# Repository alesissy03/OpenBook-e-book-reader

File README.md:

# OpenBook-e-book-reader

# Project Structure
```
OpenBook E-Reader
├── Hardware
│ ├── E-Reader.sch
│ └── E-Reader.brd
├── Manufacturing
│ ├── gerbers.zip
│ ├── bom.csv
│ └── pap.csv
├── Mechanical
│ ├── E-Reader.zip # STEP model archive
│ ├── E-Reader.f3z
│ └── OpenBook Enclosure.f3d # Enclosure model
├── Images
│ ├── 3d.png
│ ├── Schematic.png
│ ├── Board.png
│ └── Board_in_box.png
├── LICENSE # Apache 2.0
└── README.md
```

# Bill of Materials

## Component List

| Name                          | Description                                                                                           | Value        | Quantity | Link to buy| Datasheet |
|-------------------------------|----------------------------------------------------------------------------|--------------|----------|------|------------------|
| 744043680                     | IND_4828-WE-TPC_WRE                                              | 68uH         | 1        | https://mou.sr/42yVhMe     | https://www.we-online.com/components/products/datasheet/744043680.pdf |
| 112A-TAAR-RO3_ATTEND          | Micro SD Card Socket, Push-Push Type, Top Mount, SMT, H = 1.83mm | 10u          | 1        | https://www.attend.com.tw/en/product.php?act=view&id=253# | https://www.attend.com.tw/data/download/file/112A-TAAR-R03_Spec.pdf |
| BD5229G-TR                    | Voltage Detector with Adjustable Delay Time (CMOS)               |              | 1        | https://mou.sr/421TSO9     | https://fscdn.rohm.com/en/products/databook/datasheet/ic/power/voltage_detector/bd52xxg-e.pdf |
| BUTTON_CUSYOMV1               | Momentary Switch (Pushbutton) – SPST – SMD, 4.6 x 2.8mm          |              | 3        | https://mou.sr/41Yc6zX     | https://4donline.ihs.com/images/VipMasterIC/IC/PANA/PANA-S-A0000771493/PANA-S-A0000771493-1.pdf? hkey=CECEF36DEECDED6468708AAF2E19C0C6 |
| CPH3225A                      | Capacitor 0.011F 3.3V 1210 Flat                                  |              | 1        | https://mou.sr/42aoXOc     | https://ro.mouser.com/datasheet/2/360/Seiko_Instruments_MicroBattery_E_20230330_2024Jan_-3561061.pdf |
| DS3231SN#                     | Real Time Clock Serial 16-Pin SOIC W T/R                         |              | 1        | https://mou.sr/4ll9PXb     | https://ro.mouser.com/datasheet/2/609/DS3231-3421123.pdf |
| EAGLE-LTSPICE_CC0402         | Capacitor                                                         | 100nF        | 8        | https://mou.sr/42aprE0     | https://www.mouser.com/catalog/specsheets/Kemet_2-4-2024_KEM_F3140_R41D_Y2_300%20(draft3)%20(3).pdf?_gl=1*1rt35nv*_gcl_au*OTQ1MTI5Nzc4LjE3NDM5NjUwNTA.*_ga*MTkwMDk4MTgwMy4xNzQzOTY1MDUx*_ga_15W4STQT4T*MTc0NDc3OTk1NS4zLjEuMTc0NDc4MTkwNi4xOS4wLjA. |
| EAGLE-LTSPICE_CC0402         | Capacitor                                                         | 4.7uF        | 5        | https://mou.sr/44lcHNw     | https://ro.mouser.com/datasheet/2/40/AutoMLCCKAM-3216307.pdf |
| EAGLE-LTSPICE_CC0402         | Capacitor                                                         | 10uF         | 1        | https://mou.sr/3G8LNhS     | https://ro.mouser.com/datasheet/2/40/cx5r_KGM-3223198.pdf |
| EAGLE-LTSPICE_CC0402         | Capacitor                                                         | 1uF/50V      | 9        | https://mou.sr/3YwHHGK     | https://ro.mouser.com/datasheet/2/447/upy_gphc_x5r_4v_to_50v-3461255.pdf |
| EAGLE-LTSPICE_CC0402         | Capacitor                                                         | 0.1uF/50V    | 1        | https://mou.sr/3RC3wkl     | https://product.tdk.com/system/files/dam/doc/product/capacitor/ceramic/mlcc/catalog/mlcc_commercial_midvoltage_en.pdf |
| EAGLE-LTSPICE_CC0402         | Capacitor                                                         | 1nF          | 1        | https://mou.sr/3YwHHGK     | https://ro.mouser.com/datasheet/2/447/upy_gphc_x5r_4v_to_50v-3461255.pdf |
| ESP32_WROVER_BME680_BME680   | Integrated Environmental Unit (BME680)                            |              | 1        | https://mou.sr/42kgEzJ     | https://ro.mouser.com/datasheet/2/783/BST_BME680_DS001-1509608.pdf |
| ESP32_WROVER_AVX---          | Schotty Barrier Rectifier Diode                                   |              | 1        |                            |
| ESP32_WROVER_RR0402          | Resistor                                                          | 10k          | 15       | https://mou.sr/4i5Vvim     | https://www.vishay.com/docs/53046/pfrr.pdf |
| ESP32_WROVER_RR0402          | Resistor                                                          | 2.2          | 1        | https://mou.sr/4i9Xsun     | https://www.vishay.com/docs/53046/pfrr.pdf |
| ESP32_WROVER_RR0402          | Resistor                                                          | 0.47         | 1        | https://mou.sr/4i9XAKn     | https://www.vishay.com/docs/53046/pfrr.pdf |
| ESP32_WROVER_RR0402          | Resistor                                                          | 200          | 1        | https://mou.sr/4i9XAKn     | https://www.vishay.com/docs/53046/pfrr.pdf |
| ESP32_WROVER_RR0402          | Resistor                                                          | 2k           | 1        | https://mou.sr/4jeq8Do     | https://www.vishay.com/docs/53046/pfrr.pdf |
| ESP32_WROVER_RR0402          | Resistor                                                          | 15           | 1        | https://mou.sr/4i5Vvim     | https://www.vishay.com/docs/53046/pfrr.pdf |
| ESP32_WROVER_RR0402          | Resistor                                                          | 5k1          | 2        | https://mou.sr/4jeq8Do     | https://www.vishay.com/docs/53046/pfrr.pdf |
| ESP32_WROVER_RR0402          | Resistor                                                          | 100k         | 1        | https://mou.sr/4jeq8Do     | https://www.vishay.com/docs/53046/pfrr.pdf |
| ESP32_WROVER_SPARKFUN-       | P-channel MOSFETs                                                 |              | 2        | https://mou.sr/42jyNxv     | https://ro.mouser.com/datasheet/2/268/MCP73831_Family_Data_Sheet_DS20001984H-3441711.pdf |
| ESP32_WROVER_SPARKFUN-IC-    | MCP73831T Li-Ion, Li-Pol Controller                               |              | 1        | https://mou.sr/42jyNxv     | https://ro.mouser.com/datasheet/2/268/MCP73831_Family_Data_Sheet_DS20001984H-3441711.pdf |
| ESP32C6_VARISTORCN1812       | Varistor                                                          |              | 1        | https://mou.sr/3RnbVYV     | https://www.tdk-electronics.tdk.com/inf/75/db/CTVS_14/Surge_protection_series.pdf |
| ESP32-C6-WROOM-1-N8          |                                                                   |              | 1        | https://mou.sr/42swLfH     | https://ro.mouser.com/datasheet/2/891/Espressif_ESP32_C6_WROOM_1__Datasheet_V0_1_PRELIMI-3239987.pdf |
| FH34SRJ-24S-0.5SH_99_        | 24-pos FFC/FPC Connector, Right Angle                             |              | 1        |  https://mou.sr/43Cr53R    | https://ro.mouser.com/datasheet/2/185/FH34SRJ_24S_0_5SH_99__CL0580_1255_6_99_2DDrawing_0-1615044.pdf |
| MAX17048G+T10                | Fuel Gauge                                                        |              | 1        | https://mou.sr/3FWR5wY     | https://ro.mouser.com/datasheet/2/609/MAX17048_MAX17049-3469099.pdf |
| MBR0530                       | Diode, Schottky, 0.5A, 30V, SOD-123                              |              | 2        | https://mou.sr/4jmza1b     | https://www.onsemi.com/download/data-sheet/pdf/mbr0530t1-d.pdf |
| PGB1010603MR                  | ESD Suppressor                                                   |              | 6        | https://mou.sr/3Yg9sDe     | https://www.littelfuse.com/assetdocs/pulseguard-esd-suppressors-pgb1-datasheet?assetguid=8a337998-d54d-466b-be4e-dc5bcd1f9321 |
| QWIIC_CONNECTORJS-1MM        | I²C Standard Qwiic Connector                                      |              | 1        | https://www.sparkfun.com/qwiic-jst-connector-smd-4-pin-horizontal.html | https://cdn.sparkfun.com/assets/parts/1/2/2/8/9/Qwiic_Connector_Datasheet.pdf |
| RCL_CPOL-EUCT3528            | Polarized Capacitor (Tantalum)                                    | 100uF TANT   | 1        | https://mou.sr/42webCl     | https://www.mouser.com/catalog/specsheets/Panasonic_08082018_Capacitor%20Radial%20Leaded%20Lytic%20(EEU-FS)%20020118.pdf?_gl=1*1qqq4o9*_gcl_au*OTQ1MTI5Nzc4LjE3NDM5NjUwNTA.*_ga*MTkwMDk4MTgwMy4xNzQzOTY1MDUx*_ga_15W4STQT4T*MTc0NDc3OTk1NS4zLjEuMTc0NDc4MjQ0MS4zOC4wLjA. |
| SAMACSYS_USB4110-GF-A        | USB 2.0 Type-C Connector, Right Angle SMT                         |              | 1        | https://www.digikey.ro/en/products/detail/gct/USB4110-GF-A/10384547     | https://gct.co/files/specs/usb4110-spec.pdf?v=6b2a6292-70a5-4bd5-a7e5-0f3fe03e015f |
| SI1308EDL-T1-GE3              | MOSFET N-Ch 30V 1.5A Vishay TrenchFET                            |              | 1        | https://mou.sr/4lj7JXH     | https://www.vishay.com/docs/63399/si1308edl.pdf |
| SJ                            | SMD Solder Jumper                                                |              | 1        | https://mou.sr/42luaTB     | https://ro.mouser.com/datasheet/2/972/cjs-1827353.pdf |
| USBLC6-2SC6Y                 | ESD Protection Diode Array, 6-Pin SOT-23                          |              | 1        | https://mou.sr/42lyiTK     | https://ro.mouser.com/datasheet/2/389/usblc6_2sc6y-1852505.pdf |
| W25Q512JVEIQ                 | Flash Memory                                                      |              | 1        | https://mou.sr/42vsB6J     | https://ro.mouser.com/datasheet/2/949/Winbond_W25Q512JV_Datasheet-3240039.pdf |
| XC6220A331MR-G               | LDO Voltage Regulator                                             |              | 1        | https://mou.sr/4ieKgVa     | https://ro.mouser.com/ProductDetail/Torex-Semiconductor/XC6220A331MR-G?qs=AsjdqWjXhJ8ZSWznL1J0gg%3D%3D |

# ESP32 C6

| Pin        | Name | Label|  Function             | Connection to  |
|------------|-------|----------|----------------------|----------------|
| 1 | GND | - | Ground | Ground |
| 2 | 3V3 | - | Power | 3.3V |
| 3 | EN | RESET |Reset | Pull-up to 3.3v |
| 4 | IO4 | SS_SD | SD card chip select | J4 |
| 5 | IO5 | EPD_DC | E-Paper Display Command | J4 |
| 6 | IO6 | SCK | SPI Clock | J3, J4 |
| 7 | IO7 | MOSI | Master Out Slave In | J3, J4 |
| 8 | IO0 | INT_RTC | RTC Interrupt | DS3231SN |
| 9 | IO1 | 32KHZ | 32 kHz output | DS3231SN |
| 10 | IO8 | - | Power | 3.3V |
| 11 | IO10 | EPD_CS | E-Paper Display Chip Select | J3 |
| 12 | IO11 | FLASH_CS | Exernal NOR Flash Chip Select | J4 |
| 13 | IO12 | USB_D- | USB D- | J2 via D2 |
| 14 | IO13 | USB_D+ | USB D+ | J2 via D2 |
| 15 | IO9 | IO/BOOT | BOOT button | BOOT button
| 16 | IO18 | RTC_RST | RTC Module Reset | DS3231SN |
| 17 | IO19 | I2C_PW | Power | BME688 Sensor |
| 18 | IO20 | EPD_3V3_C | E-Paper Display Power | 
| 19 | IO21 | SDA | Battery Level
| 20 | IO22 | SCL | Battery Level
| 21 | IO23 | EPD_RST | E-Paper Display Reset | J4
| 22 | NC | - | - | -
| 23 | IO15 | IO/CHANGE | Change button | Change Button
| 24 | RXD0/GPIO17 | RX | UART EX
| 25 | TXD0/GPIO16 | TX | UART TX
| 26 | IO3 | EPD_BUSY | E-Paper Display Busy signal | J4
| 27 | IO2 | MISO | Master In Slave Out | J3, J4   

# Errors and warnings
During the design process in Autodesk Fusion, several warnings were flagged in both the schematic and PCB layouts. Below is a summary of the warnings I reviewed and explicitly approved based on the context of this project:

## Schematic (only warnings, no errors)
### "POWER pin X connected to Y" Warnings
- VBAT is supplied via a battery circuit
- 3V3 is regulated by a dedicated LDO
- I2C_PW and other power rails are driven by appropriate sources
- All GND connections are correctly tied to a common ground plane
- POWER pin U3 VBAT connected to VRTC is intentional, VRTC is your battery backup supply for the RTC
- POWER pin SENSOR2 VDDIO connected to I2C_PW / POWER pin SENSOR2 VDD connected to I2C_PW: these refer to the BME680 sensor (SENSOR2), which uses VDD for logic and VDDIO for I/O voltage levels
- POWER pin MCP73831 VIN connected to VBUS: the MCP73831 is a Li-Ion battery charger, and VIN is supposed to be connected to a power input, like USB VBUS
### "Part X has no value" Warnings
- Those parts are supposed not to have value (for example the frame)

## Board
- Smd-Hole, Board Outline-Clearance error (at USB C connector): ok to approved as per instructions given
- Copper width errors (1 data wire, 3 power wires): approved because I manually checked the wire and it has the desired width

_Disclaimer: This project was done using Fusion in browser._

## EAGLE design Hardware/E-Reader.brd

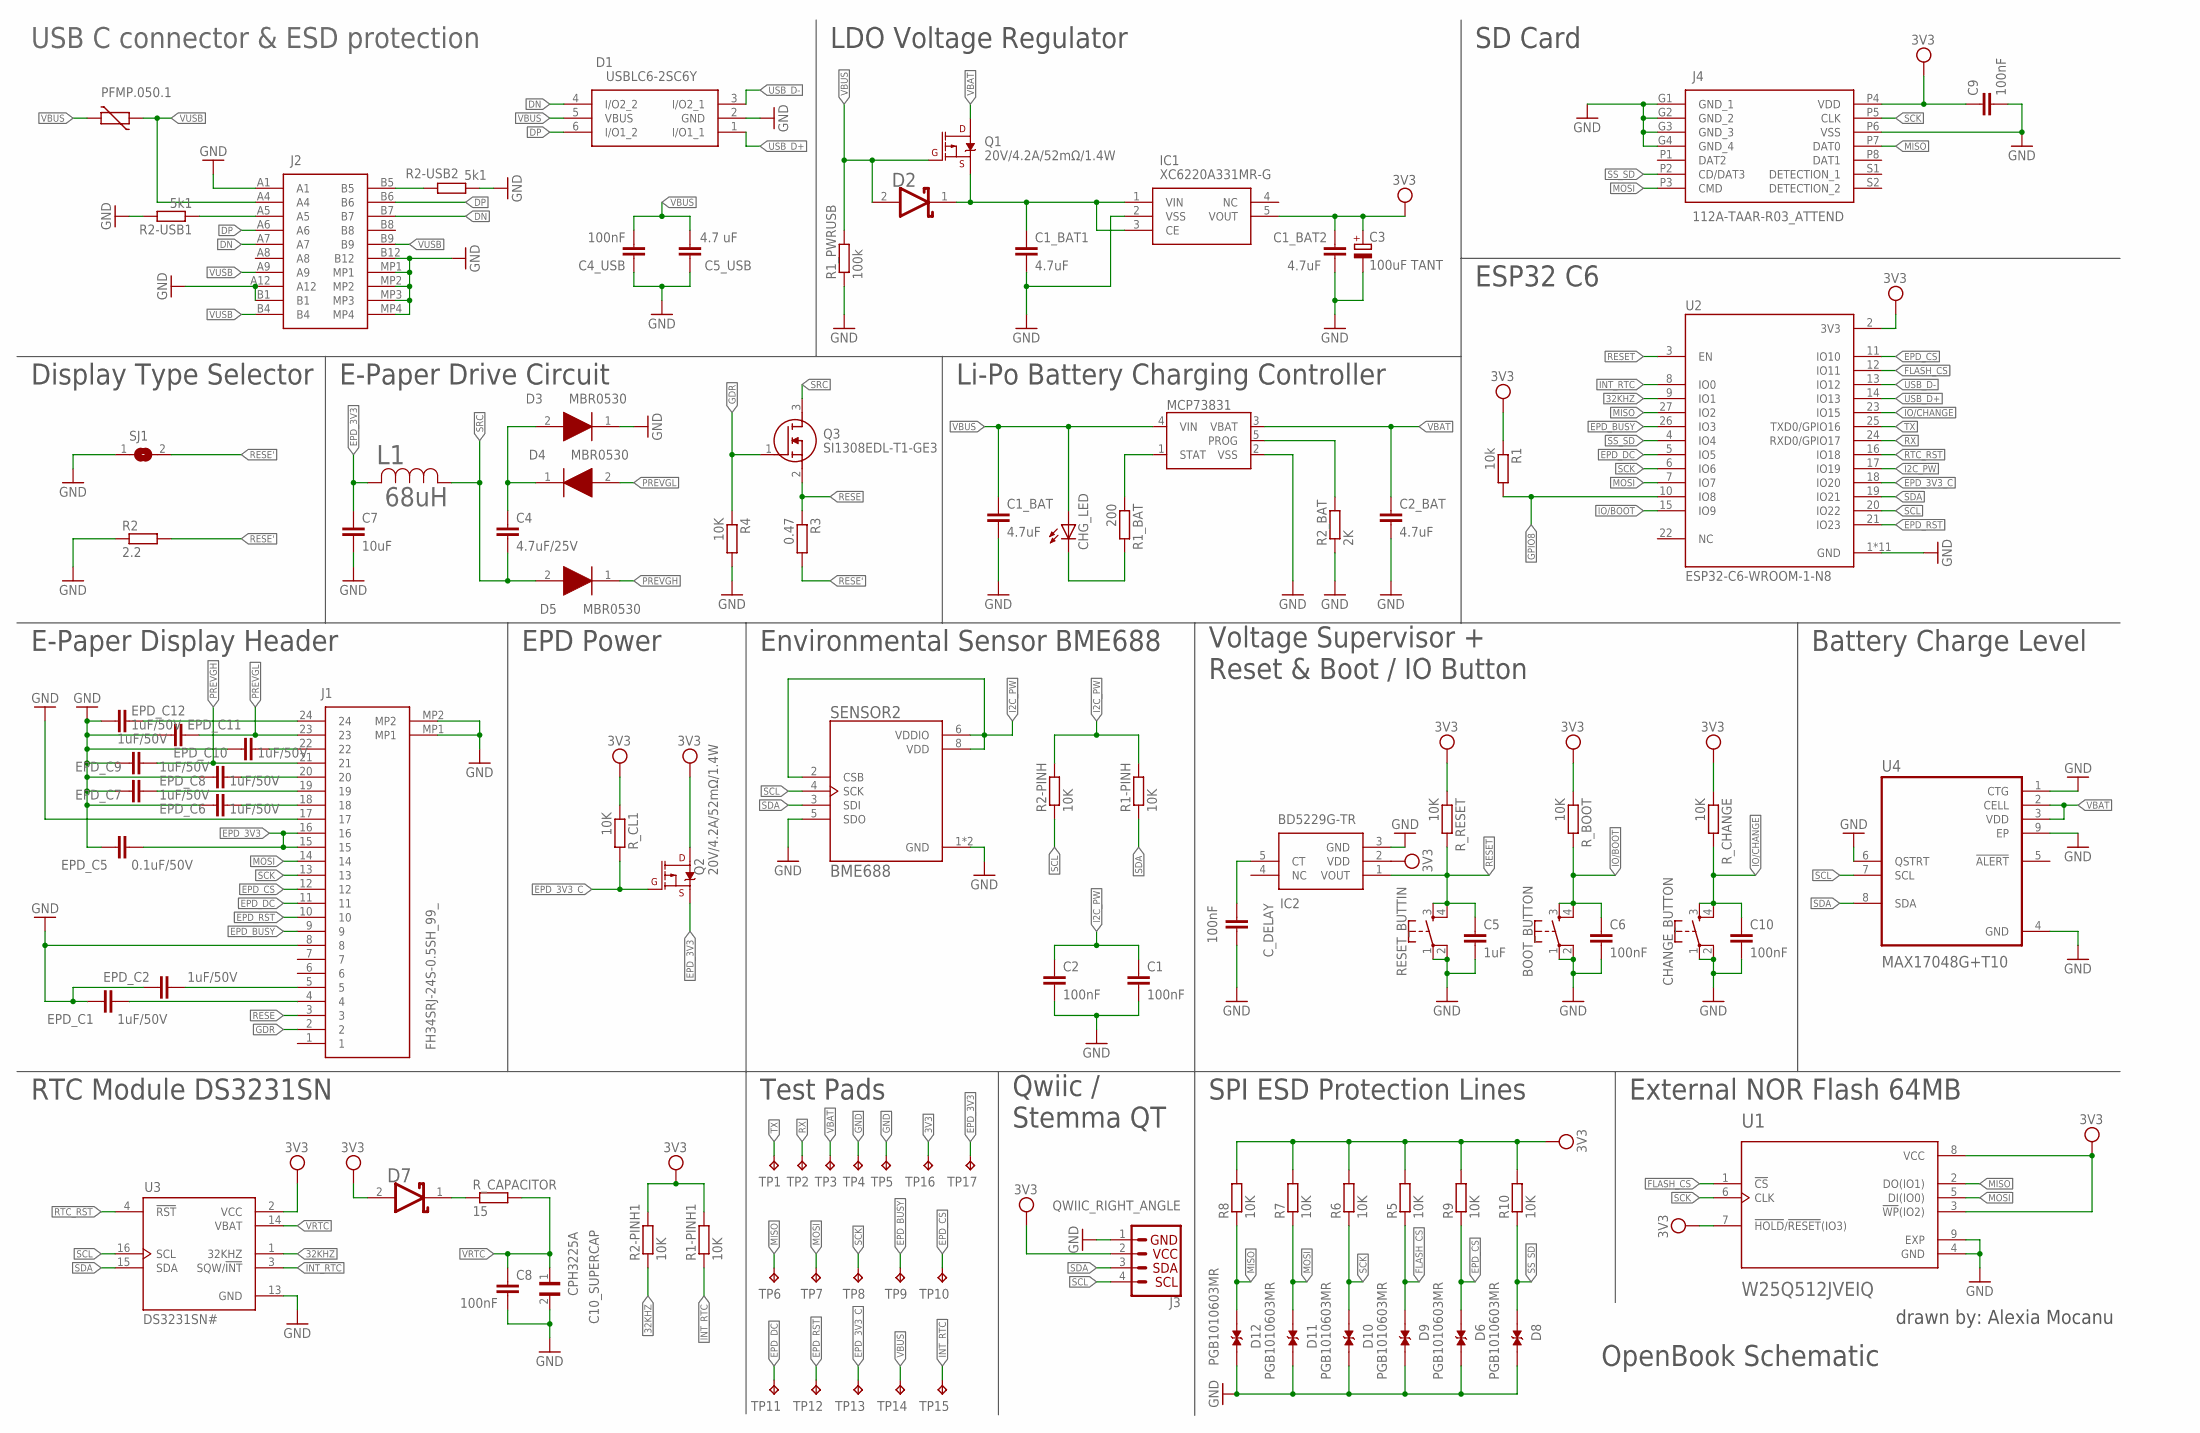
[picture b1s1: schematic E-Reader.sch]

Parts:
BOOT_BUTTON: BUTTON_CUSYOMV1; MYBUTTON
C1, C2, C4_USB, C6, C8, C9, C10: 100nF; EAGLE-LTSPICE_C0402
C1_BAT, C1_BAT1, C1_BAT2, C2_BAT: 4.7uF; EAGLE-LTSPICE_C0402
C3: 100uF TANT; RCL_CT3528
C4: 4.7uF/25V; EAGLE-LTSPICE_C0402
C5: 1uF; EAGLE-LTSPICE_C0402
C5_USB: 4.7 uF; EAGLE-LTSPICE_C0402
C7: 10uF; EAGLE-LTSPICE_C0402
C10_SUPERCAP: CPH3225A; CAPCP3225X100N
CHANGE_BUTTON: BUTTON_CUSYOMV1; MYBUTTON
CHG_LED: ADAFRUIT_LEDCHIP-LED0603; ADAFRUIT_CHIP-LED0603
C_DELAY: 100nF; EAGLE-LTSPICE_C0402
D1: USBLC6-2SC6Y; SOT95P280X145-6N
D2: ESP32_WROVER_AVX---SD0805S020S1R0_AVX_SD0805S020S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; ESP32_WROVER_AVX---SD0805S020S1R0_AVX_SD0805S020S1R0_0
D3, D4, D5: MBR0530; SOD3716X135N
D6, D8, D9, D10, D11, D12: PGB1010603MR; DIOC1608X36N
D7: SD0805S020S1R0; ESP32_WROVER_AVX---SD0805S020S1R0_AVX_SD0805S020S1R0_0
EPD_C1, EPD_C2, EPD_C6, EPD_C7, EPD_C8, EPD_C9, EPD_C10, EPD_C11, EPD_C12: 1uF/50V; EAGLE-LTSPICE_C0402
EPD_C5: 0.1uF/50V; EAGLE-LTSPICE_C0402
IC1: XC6220A331MR-G; SOT95P280X120-5N
IC2: BD5229G-TR; SOT95P280X125-5N
J1: FH34SRJ-24S-0.5SH_99_; FH34SRJ24S05SH99
J2: SAMACSYS_PARTS_USB4110-GF-A; SAMACSYS_PARTS_USB4110GFA
J3: QWIIC_RIGHT_ANGLE; JST04_1MM_RA
J4: 112A-TAAR-R03_ATTEND; 112ATAARR03ATTEND
L1: 68uH; IND_4828-WE-TPC_WRE
MCP73831: ESP32_WROVER_SPARKFUN-IC-POWER_MCP73831; ESP32_WROVER_SPARKFUN-IC-POWER_SOT23-5
PFMP.050.1: ESP32C6_VARISTORCN1812; ESP32C6_VARISTOR_CT/CN1812
Q1, Q2: 20V/4.2A/52mΩ/1.4W; ESP32_WROVER_SPARKFUN-DISCRETESEMI_SOT23-3
Q3: SI1308EDL-T1-GE3; SOT65P210X110-3N
R1: 10k; ESP32_WROVER_EAGLE-LTSPICE_R0402
R1-PINH, R1-PINH1, R2-PINH, R2-PINH1, R4, R5, R6, R7, R8, R9, R10: 10K; ESP32_WROVER_EAGLE-LTSPICE_R0402
R1_BAT: 200; ESP32_WROVER_EAGLE-LTSPICE_R0402
R1_PWRUSB: 100k; ESP32_WROVER_EAGLE-LTSPICE_R0402
R2: 2.2; ESP32_WROVER_EAGLE-LTSPICE_R0402
R2-USB1, R2-USB2: 5k1; ESP32_WROVER_EAGLE-LTSPICE_R0402
R2_BAT: 2K; ESP32_WROVER_EAGLE-LTSPICE_R0402
R3: 0.47; ESP32_WROVER_EAGLE-LTSPICE_R0402
RESET_BUTTIN: BUTTON_CUSYOMV1; MYBUTTON
R_BOOT: 10K; ESP32_WROVER_EAGLE-LTSPICE_R0402
R_CAPACITOR: 15; ESP32_WROVER_EAGLE-LTSPICE_R0402
R_CHANGE: 10K; ESP32_WROVER_EAGLE-LTSPICE_R0402
R_CL1: 10K; ESP32_WROVER_EAGLE-LTSPICE_R0402
R_RESET: 10K; ESP32_WROVER_EAGLE-LTSPICE_R0402
SENSOR2: BME688; ESP32_WROVER_BME680_PSON80P300X300X100-8N
SJ1: SJ
TP1, TP2, TP3, TP4, TP5, TP6, TP7, TP8, TP9, TP10, TP11, TP12, TP13, TP14, TP15, TP16, TP17: TPTP20R; TP20R
U1: W25Q512JVEIQ; SON127P600X800X80-9N
U2: ESP32-C6-WROOM-1-N8; XCVR_ESP32-C6-WROOM-1-N8
U3: DS3231SN#; SOIC127P1032X265-16N
U4: MAX17048G+T10; SON50P200X200X80-9N

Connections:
3V3: C1_BAT2.1, C3.+, C9.1, D7.2 (ANODE), IC1.5 (VOUT), IC2.2 (VDD), J3.2, J4.P4 (VDD), Q2.3 (D), R1.1, R1-PINH1.2, R2-PINH1.2, R5.2, R6.2, R7.2, R8.2, R9.2, R10.2, R_BOOT.1, R_CHANGE.1, R_CL1.1, R_RESET.1, TP16.TP, U1.3 (!WP!(IO2)), U1.7 (!HOLD!/!RESET!(IO3)), U1.8 (VCC), U2.2 (3V3), U3.2 (VCC)
32KHZ: R2-PINH1.1, U2.9 (IO1), U3.1 (32KHZ)
DN: D1.4 (I/O2_2), J2.A7, J2.B7
DP: D1.6 (I/O1_2), J2.A6, J2.B6
EPD_3V3: C7.1, EPD_C5.1, J1.15, J1.16, L1.2, Q2.2 (S), TP17.TP
EPD_3V3_C: Q2.1 (G), R_CL1.2, TP13.TP, U2.18 (IO20)
EPD_BUSY: J1.9, TP9.TP, U2.26 (IO3)
EPD_CS: D6.1, J1.12, R9.1, TP10.TP, U2.11 (IO10)
EPD_DC: J1.11, TP11.TP, U2.5 (IO5)
EPD_RST: J1.10, TP12.TP, U2.21 (IO23)
FLASH_CS: D9.1, R5.1, U1.1 (!CS), U2.12 (IO11)
GDR: J1.2, Q3.1 (G), R4.1
GND: BOOT_BUTTON.1, BOOT_BUTTON.2, C1.2, C1_BAT.2, C1_BAT1.2, C1_BAT2.2, C2.2, C2_BAT.2, C3.-, C4_USB.1, C5.2, C5_USB.1, C6.2, C7.2, C8.2, C9.2, C10.2, C10_SUPERCAP.2, CHANGE_BUTTON.1, CHANGE_BUTTON.2, C_DELAY.2, D1.2 (GND), D3.1 (K), D6.2, D8.2, D9.2, D10.2, D11.2, D12.2, EPD_C1.2, EPD_C2.2, EPD_C5.2, EPD_C6.2, EPD_C7.2, EPD_C8.2, EPD_C9.2, EPD_C10.2, EPD_C11.2, EPD_C12.2, IC1.2 (VSS), IC2.3 (GND), J1.8, J1.17, J1.MP1, J1.MP2, J2.A1, J2.A12, J2.B1, J2.B12, J2.MP1, J2.MP2, J2.MP3, J2.MP4, J3.1, J4.G1 (GND_1), J4.G2 (GND_2), J4.G3 (GND_3), J4.G4 (GND_4), J4.P6 (VSS), MCP73831.2 (VSS), R1_PWRUSB.1, R2.1, R2-USB1.2, R2-USB2.1, R2_BAT.1, R4.2, RESET_BUTTIN.1, RESET_BUTTIN.2, SENSOR2.1 (GND), SENSOR2.5 (SDO), SENSOR2.7 (GND), SJ1.1, TP4.TP, TP5.TP, U1.4 (GND), U1.9 (EXP), U2.1 (GND), U2.28 (GND), U2.29_1 (GND), U2.29_2 (GND), U2.29_3 (GND), U2.29_4 (GND), U2.29_5 (GND), U2.29_6 (GND), U2.29_7 (GND), U2.29_8 (GND), U2.29_9 (GND), U3.13 (GND), U4.1 (CTG), U4.4 (GND), U4.6 (QSTRT), U4.9 (EP)
GPIO8: R1.2, U2.10 (IO8)
I2C_PW: C1.1, C2.1, R1-PINH.2, R2-PINH.2, SENSOR2.2 (CSB), SENSOR2.6 (VDDIO), SENSOR2.8 (VDD), U2.17 (IO19)
INT_RTC: R1-PINH1.1, TP15.TP, U2.8 (IO0), U3.3 (SQW/!INT)
IO/BOOT: BOOT_BUTTON.3, BOOT_BUTTON.4, C6.1, R_BOOT.2, U2.15 (IO9)
IO/CHANGE: C10.1, CHANGE_BUTTON.3, CHANGE_BUTTON.4, R_CHANGE.2, U2.23 (IO15)
MISO: D12.1, J4.P7 (DAT0), R8.1, TP6.TP, U1.2 (DO(IO1)), U2.27 (IO2)
MOSI: D11.1, J1.14, J4.P3 (CMD), R7.1, TP7.TP, U1.5 (DI(IO0)), U2.7 (IO7)
unnamed: C1_BAT1.1, D2.1 (CATHODE), IC1.1 (VIN), IC1.3 (CE), Q1.2 (S)
unnamed: J2.A5, R2-USB1.1
unnamed: EPD_C12.1, J1.24
unnamed: C_DELAY.1, IC2.5 (CT)
unnamed: C4.1, D3.2 (A), D4.1 (K)
unnamed: MCP73831.1 (STAT), R1_BAT.1
unnamed: CHG_LED.C, R1_BAT.2
unnamed: J2.B5, R2-USB2.2
unnamed: MCP73831.5 (PROG), R2_BAT.2
unnamed: EPD_C10.1, J1.22
unnamed: EPD_C8.1, J1.20
unnamed: EPD_C7.1, J1.19
unnamed: EPD_C6.1, J1.18
unnamed: EPD_C1.1, J1.4
unnamed: EPD_C2.1, J1.5
unnamed: D7.1 (CATHODE), R_CAPACITOR.1
PREVGH: D5.1 (K), EPD_C9.1, J1.21
PREVGL: D4.2 (A), EPD_C11.1, J1.23
RESE: J1.3, Q3.2 (S), R3.1
RESE': R2.2, R3.2, SJ1.2
RESET: C5.1, IC2.1 (VOUT), RESET_BUTTIN.3, RESET_BUTTIN.4, R_RESET.2, U2.3 (EN)
RTC_RST: U2.16 (IO18), U3.4 (!RST)
RX: TP2.TP, U2.24 (RXD0/GPIO17)
SCK: D10.1, J1.13, J4.P5 (CLK), R6.1, TP8.TP, U1.6 (CLK), U2.6 (IO6)
SCL: J3.4, R2-PINH.1, SENSOR2.4 (SCK), U2.20 (IO22), U3.16 (SCL), U4.7 (SCL)
SDA: J3.3, R1-PINH.1, SENSOR2.3 (SDI), U2.19 (IO21), U3.15 (SDA), U4.8 (SDA)
SRC: C4.2, D5.2 (A), L1.1, Q3.3 (D)
SS_SD: D8.1, J4.P2 (CD/DAT3), R10.1, U2.4 (IO4)
TX: TP1.TP, U2.25 (TXD0/GPIO16)
USB_D+: D1.1 (I/O1_1), U2.14 (IO13)
USB_D-: D1.3 (I/O2_1), U2.13 (IO12)
VBAT: C2_BAT.1, MCP73831.3 (VBAT), Q1.3 (D), TP3.TP, U4.2 (CELL), U4.3 (VDD)
VBUS: C1_BAT.1, C4_USB.2, C5_USB.2, CHG_LED.A, D1.5 (VBUS), D2.2 (ANODE), MCP73831.4 (VIN), PFMP.050.1.2, Q1.1 (G), R1_PWRUSB.2, TP14.TP
VRTC: C8.1, C10_SUPERCAP.1, R_CAPACITOR.2, U3.14 (VBAT)
VUSB: J2.A4, J2.A9, J2.B4, J2.B9, PFMP.050.1.1

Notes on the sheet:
USB C connector & ESD protection
LDO Voltage Regulator
SD Card
ESP32 C6
Display Type Selector
E-Paper Drive Circuit
Li-Po Battery Charging Controller
E-Paper Display Header
EPD Power
Environmental Sensor BME688
Voltage Supervisor + Reset & Boot / IO Button
Battery Charge Level
RTC Module DS3231SN
Test Pads
Qwiic / Stemma QT
SPI ESD Protection Lines
External NOR Flash 64MB
drawn by: Alexia Mocanu
OpenBook Schematic

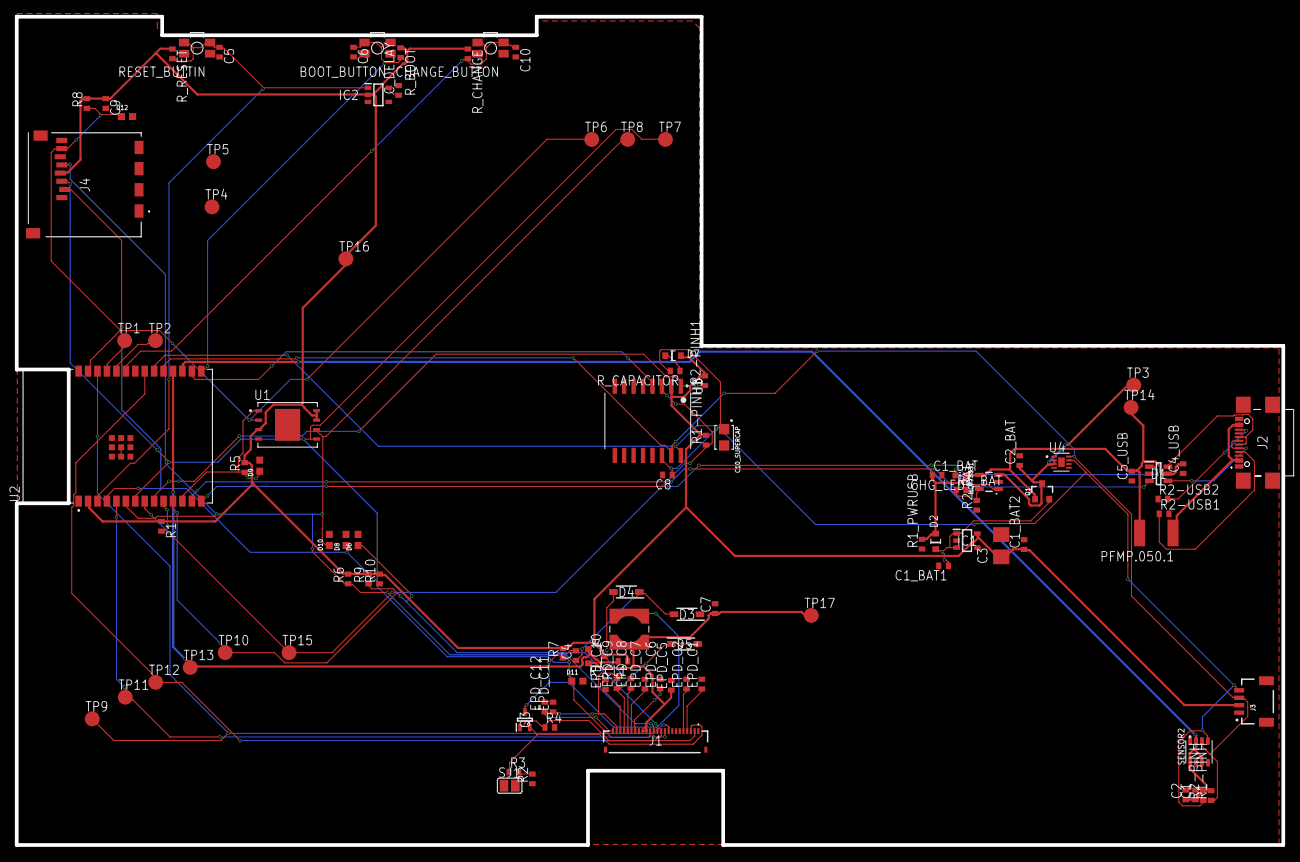
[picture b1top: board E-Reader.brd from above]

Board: 2 copper layers, 170.5 x 111.5 mm, 103 parts (0 on the bottom side), 55 nets.

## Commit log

2025-04-06 Update README.md
    Added BOM
2025-04-06 Create LICENSE
2025-04-06 Update LICENSE
2025-04-16 Resolved Issues

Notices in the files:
parts and their libraries:
COPYRIGHT: Copyright (C) 2024 Ultra Librarian. All rights reserved.
